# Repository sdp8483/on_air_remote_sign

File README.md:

# On Air Remote Sign

Project abandoned due to issues with NRF24L01+ remote power and loss of interest.
FW not finished and does not support a wireless remote, old code is in main.bak

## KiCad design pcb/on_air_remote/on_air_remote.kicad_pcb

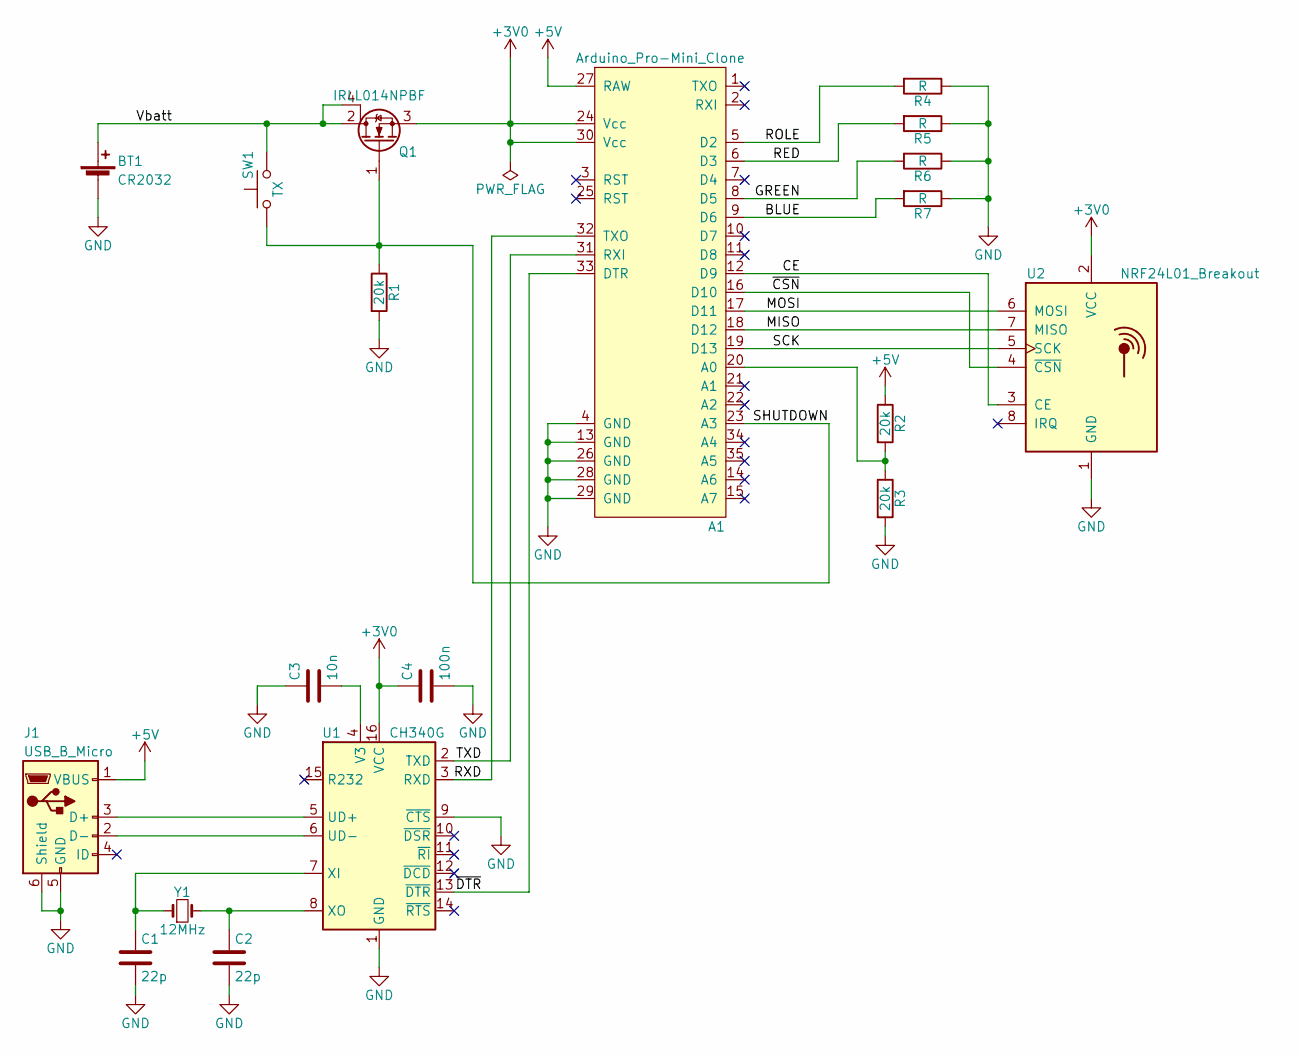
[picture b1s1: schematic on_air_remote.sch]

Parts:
A1: Arduino_Pro-Mini_Clone; Arduino_Pro-Mini-Clone
BT1: CR2032; BatteryHolder_Keystone_103_1x20mm
C1, C2: 22p; C_0805_2012Metric_Pad1.18x1.45mm_HandSolder
C3: 10n; C_0805_2012Metric_Pad1.18x1.45mm_HandSolder
C4: 100n; C_0805_2012Metric_Pad1.18x1.45mm_HandSolder
J1: USB_B_Micro; USB_Micro-B_Molex-105017-0001
Q1: IRLL014NPBF; SOT-223
R1, R2, R3: 20k; R_0805_2012Metric_Pad1.20x1.40mm_HandSolder
R4, R5, R6, R7: R; R_0805_2012Metric_Pad1.20x1.40mm_HandSolder
SW1: TX; Bright_TSA123G60-250
U1: CH340G; SOIC-16_3.9x9.9mm_P1.27mm
U2: NRF24L01_Breakout; nRF24L01_Breakout
Y1: 12MHz; Crystal_HC49-4H_Vertical

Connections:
+3V0: A1.24 (Vcc), A1.30 (Vcc), C4.1, Q1.3 (S), U1.16 (VCC), U2.2 (VCC)
+5V: A1.27 (RAW), J1.1 (VBUS), R2.1
/BLUE: A1.9 (D6), R7.2
/CE: A1.12 (D9), U2.3 (CE)
/GREEN: A1.8 (D5), R6.2
/MISO: A1.18 (D12), U2.7 (MISO)
/MOSI: A1.17 (D11), U2.6 (MOSI)
/RED: A1.6 (D3), R5.2
/ROLE: A1.5 (D2), R4.2
/RXD: A1.32 (TXO), U1.3 (RXD)
/SCK: A1.19 (D13), U2.5 (SCK)
/SHUTDOWN: A1.23 (A3), Q1.1 (G), R1.1, SW1.1
/TXD: A1.31 (RXI), U1.2 (TXD)
/Vbatt: BT1.1 (+), Q1.2 (D), Q1.4 (D), SW1.2
/~CSN: A1.16 (D10), U2.4 (~CSN)
/~DTR: A1.33 (DTR), U1.13 (~DTR)
GND: A1.4 (GND), A1.13 (GND), A1.26 (GND), A1.28 (GND), A1.29 (GND), BT1.2 (-), C1.2, C2.2, C3.1, C4.2, J1.5 (GND), J1.6 (Shield), R1.2, R3.2, R4.1, R5.1, R6.1, R7.1, U1.1 (GND), U1.9 (~CTS), U2.1 (GND)
unnamed: A1.20 (A0), R2.2, R3.1
unnamed: C1.1, U1.7 (XI), Y1.1
unnamed: C2.1, U1.8 (XO), Y1.2
unnamed: C3.2, U1.4 (V3)
unnamed: J1.2 (D-), U1.6 (UD-)
unnamed: J1.3 (D+), U1.5 (UD+)

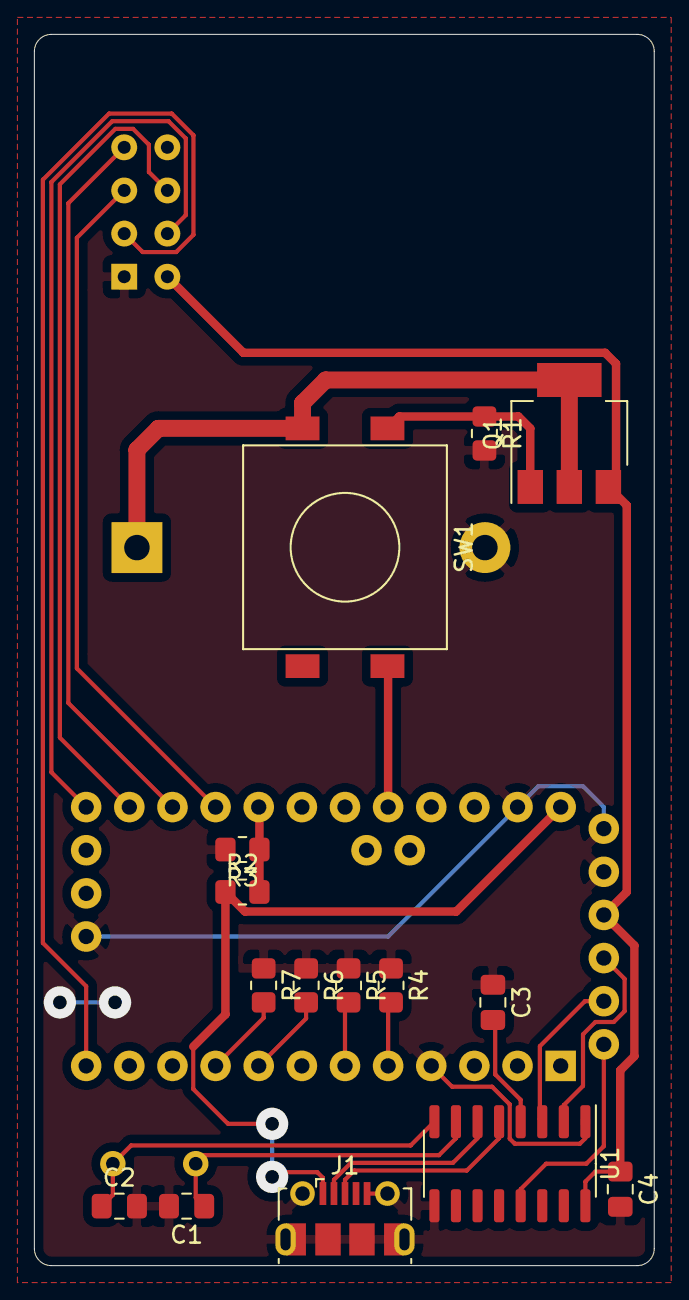
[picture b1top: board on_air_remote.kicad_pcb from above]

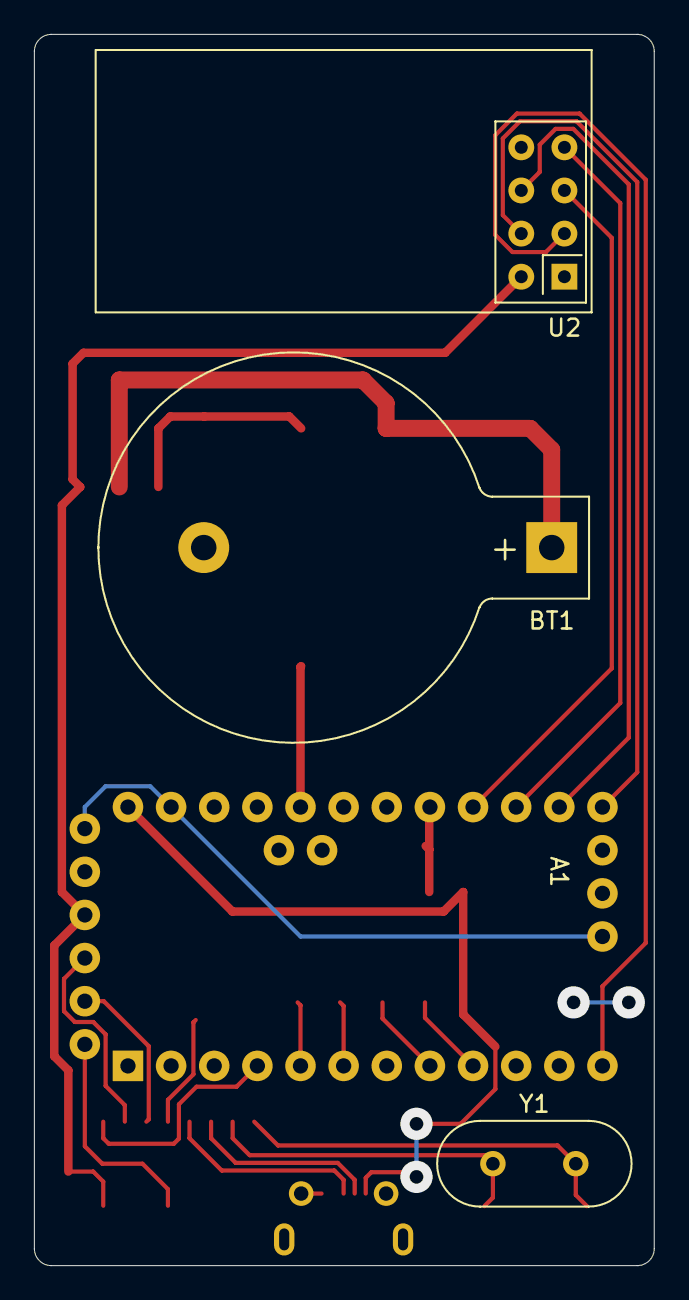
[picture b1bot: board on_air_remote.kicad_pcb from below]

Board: 2 copper layers, 36.5 x 72.5 mm, 19 parts (4 on the bottom side), 23 nets.

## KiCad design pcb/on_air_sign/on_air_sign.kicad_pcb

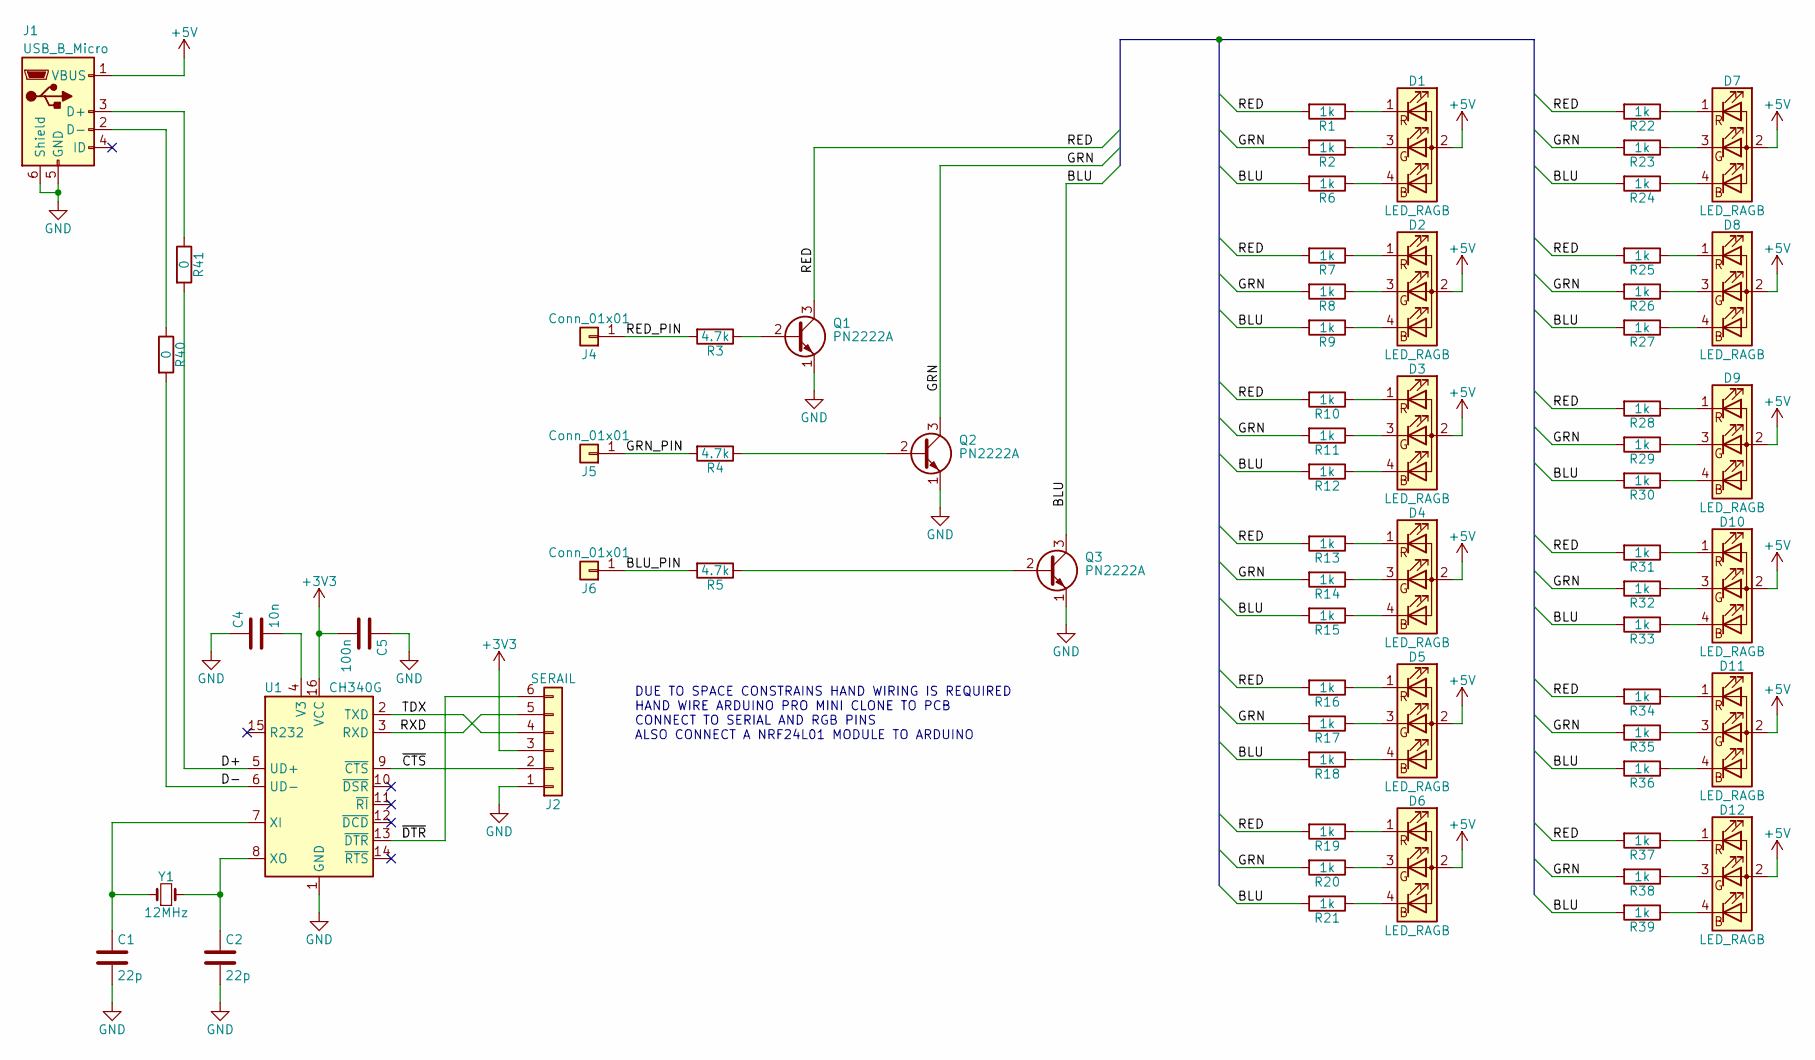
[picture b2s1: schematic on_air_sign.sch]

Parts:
C1, C2: 22p; C_Disc_D3.8mm_W2.6mm_P2.50mm
C4: 10n; C_0603_1608Metric_Pad1.08x0.95mm_HandSolder
C5: 100n; C_Disc_D4.3mm_W1.9mm_P5.00mm
D1, D2, D3, D4, D5, D6, D7, D8, D9, D10, D11, D12: LED_RAGB; LED_D5.0mm-4_RGB_Staggered_Pins
J1: USB_B_Micro; USB_Micro-B_GCT_USB3076-30-A
J2: SERAIL; PinHeader_1x06_P2.54mm_Vertical
J4, J5, J6: Conn_01x01; TestPoint_Pad_2.5x2.5mm
Q1, Q2, Q3: PN2222A; TO-92_Inline
R1, R2, R6, R7, R8, R9, R10, R11, R12, R13, R14, R15, R16, R17, R18, R19, R20, R21, R22, R23, R24, R25, R26, R27, R28, R29, R30, R31, R32, R33, R34, R35, R36, R37, R38, R39: 1k; R_Axial_DIN0204_L3.6mm_D1.6mm_P7.62mm_Horizontal
R3, R4, R5: 4.7k; R_Axial_DIN0204_L3.6mm_D1.6mm_P7.62mm_Horizontal
R40, R41: 0; R_0805_2012Metric_Pad1.20x1.40mm_HandSolder
U1: CH340G; SOIC-16_3.9x9.9mm_P1.27mm
Y1: 12MHz; Crystal_HC49-4H_Vertical

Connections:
+3V3: C5.2, J2.3, U1.16 (VCC)
+5V: D1.2 (A), D2.2 (A), D3.2 (A), D4.2 (A), D5.2 (A), D6.2 (A), D7.2 (A), D8.2 (A), D9.2 (A), D10.2 (A), D11.2 (A), D12.2 (A), J1.1 (VBUS)
/BLU: Q3.3 (C), R6.2, R9.2, R12.2, R15.2, R18.2, R21.2, R24.2, R27.2, R30.2, R33.2, R36.2, R39.2
/BLU_PIN: J6.1, R5.2
/D+: R41.2, U1.5 (UD+)
/D-: R40.2, U1.6 (UD-)
/GRN: Q2.3 (C), R2.2, R8.2, R11.2, R14.2, R17.2, R20.2, R23.2, R26.2, R29.2, R32.2, R35.2, R38.2
/GRN_PIN: J5.1, R4.2
/RED: Q1.3 (C), R1.2, R7.2, R10.2, R13.2, R16.2, R19.2, R22.2, R25.2, R28.2, R31.2, R34.2, R37.2
/RED_PIN: J4.1, R3.2
/RXD: J2.5, U1.3 (RXD)
/TDX: J2.4, U1.2 (TXD)
/~CTS: J2.2, U1.9 (~CTS)
/~DTR: J2.6, U1.13 (~DTR)
GND: C1.2, C2.2, C4.1, C5.1, J1.5 (GND), J1.6 (Shield), J2.1, Q1.1 (E), Q2.1 (E), Q3.1 (E), U1.1 (GND)
unnamed: C1.1, U1.7 (XI), Y1.1
unnamed: C2.1, U1.8 (XO), Y1.2
unnamed: C4.2, U1.4 (V3)
unnamed: D1.1 (RK), R1.1
unnamed: D1.3 (GK), R2.1
unnamed: D1.4 (BK), R6.1
unnamed: D2.1 (RK), R7.1
unnamed: D2.3 (GK), R8.1
unnamed: D2.4 (BK), R9.1
unnamed: D3.1 (RK), R10.1
unnamed: D3.3 (GK), R11.1
unnamed: D3.4 (BK), R12.1
unnamed: D4.1 (RK), R13.1
unnamed: D4.3 (GK), R14.1
unnamed: D4.4 (BK), R15.1
unnamed: D5.1 (RK), R16.1
unnamed: D5.3 (GK), R17.1
unnamed: D5.4 (BK), R18.1
unnamed: D6.1 (RK), R19.1
unnamed: D6.3 (GK), R20.1
unnamed: D6.4 (BK), R21.1
unnamed: D7.1 (RK), R22.1
unnamed: D7.3 (GK), R23.1
unnamed: D7.4 (BK), R24.1
unnamed: D8.1 (RK), R25.1
unnamed: D8.3 (GK), R26.1
unnamed: D8.4 (BK), R27.1
unnamed: D9.1 (RK), R28.1
unnamed: D9.3 (GK), R29.1
unnamed: D9.4 (BK), R30.1
unnamed: D10.1 (RK), R31.1
unnamed: D10.3 (GK), R32.1
unnamed: D10.4 (BK), R33.1
unnamed: D11.1 (RK), R34.1
unnamed: D11.3 (GK), R35.1
unnamed: D11.4 (BK), R36.1
unnamed: D12.1 (RK), R37.1
unnamed: D12.3 (GK), R38.1
unnamed: D12.4 (BK), R39.1
unnamed: J1.2 (D-), R40.1
unnamed: J1.3 (D+), R41.1
unnamed: Q1.2 (B), R3.1
unnamed: Q2.2 (B), R4.1
unnamed: Q3.2 (B), R5.1

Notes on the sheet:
DUE TO SPACE CONSTRAINS HAND WIRING IS REQUIRED HAND WIRE ARDUINO PRO MINI CLONE TO PCB CONNECT TO SERIAL AND RGB PINS ALSO CONNECT A NRF24L01 MODULE TO ARDUINO

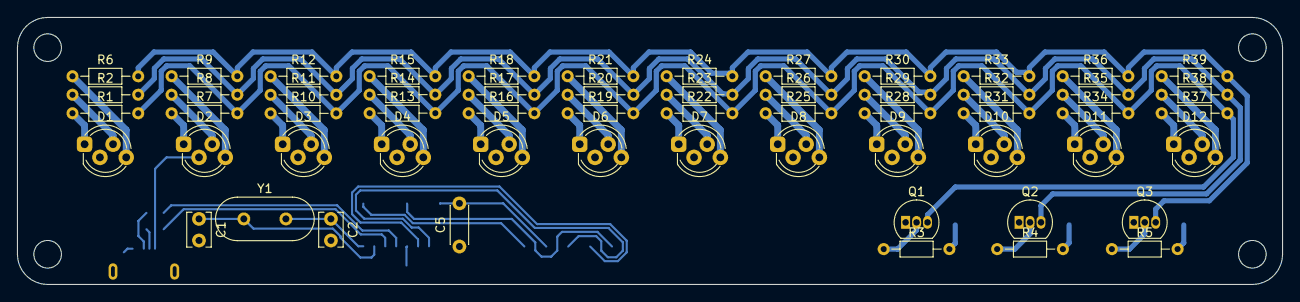
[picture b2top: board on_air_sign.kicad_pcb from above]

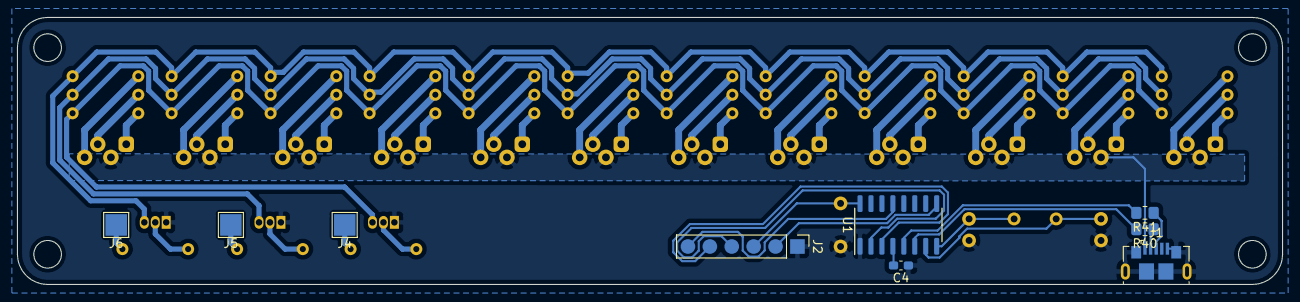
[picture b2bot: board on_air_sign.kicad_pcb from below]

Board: 2 copper layers, 146.7 x 31.0 mm, 67 parts (9 on the bottom side), 59 nets.

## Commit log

2020-11-16 init empty commit
2020-11-20 create schematic
2020-11-21 assign footprints
2020-11-21 simplify schematic
2020-11-22 add 3d model
2020-11-22 update schema and board shape
2020-11-22 plot gerbers
2020-11-22 generate gcode
2020-11-22 add pcb
2020-11-23 create sign gcode
2020-11-23 create cnc files
2020-11-24 remove freecad CAM
2020-11-25 update base
2020-11-30 increase slot size
2020-12-01 initial fw
2020-12-02 create remote pcb
2020-12-03 change shutdown pin
2020-12-03 single sided pcb done, ready for mill
2020-12-05 create gcode
2020-12-05 add v ext pin
2020-12-05 retransmit if fail
2020-12-05 sinmple fw
